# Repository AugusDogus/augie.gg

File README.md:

# augie.gg

My personal website.

## Tech Stack

- [Next.js 16](https://nextjs.org)
- [Tailwind CSS](https://tailwindcss.com)
- [Radix UI](https://www.radix-ui.com) primitives
- [MDX](https://mdxjs.com)
- [sugar-high](https://github.com/huozhi/sugar-high)
- [Phosphor Icons](https://phosphoricons.com)
- Inter and Geist Mono, self-hosted with their OFL licenses

## Projects

The home page is generated from [`src/content/projects.ts`](src/content/projects.ts),
the only file to edit.

To add a project, insert an entry in date order (newest first):

```ts
{
  title: "my-project",
  href: "https://github.com/AugusDogus/my-project", // omit for private repos
  date: "2026-10-11", // first authored commit
  blurb: "One sentence. Inline [links](https://example.com) work.",
  labels: ["wip"], // wip | active | archived | oss | pending
  private: true, // shows a private repository note
  fork: true, // name upstream in the blurb
},
```

Everything lands in the expandable Everything else section, grouped by year, unless you mark it:

- `featured: n` moves it into **Selected work** at position `n` (1 is first).
  Add a `highlight`: one line of concrete, verifiable evidence such as the
  stack, a hard problem, or real usage. Don't invent numbers.
- `notable: n` names a merged upstream contribution at position `n` of the OSS
  line under Selected work. Set `contributionName` for its short display label
  and link `href` directly to the merged PR. It also stays in Everything else.

## Development

```bash
bun install
bun dev
```

No environment variables are required. To show the GitHub activity graph, set
`GITHUB_TOKEN` to a classic personal access token with no scopes (see
`.env.example`); without it the panel is hidden and the rest of the page is
unchanged.

```bash
bun run check
bun test
bun run format:check
bun run build
```

## Design and artwork

The interface is dark glass (`.material` in `src/styles/globals.css`) over a
scrim that leaves the painting clear on the right. Inter's display cut sets the
name; Geist Mono only draws keyboard hints.

- ⌘K (or Ctrl K, or /) opens a command menu over actions, selected work, open
  source contributions, and every other project.
- Every project opens in one project view (`ProjectView` in
  `src/components/work/project-view.tsx`): its captures on top, then status,
  title, start date, blurb, evidence, and a link out. Rows, the command menu,
  the archive, and `?p=<title>` links all open it.
- On wide screens with a mouse the view lives on a stage beside the list,
  over the painting. Hovering or focusing a row previews the project there;
  clicking it or pressing Enter pins it, which selects the row, adds previous,
  next, and close buttons, writes `?p=`, and lets ← → step and Esc close.
  While a project is pinned, hovering other rows leaves the stage alone. The
  pointer can cross from a row onto the stage, even diagonally over other
  rows, without losing the preview.
- On phones, tablets, and narrow windows rows carry a thumbnail instead, and
  the same view opens in a draggable bottom sheet.
- Captures share one frame whether they are images or videos, with a phone
  capture set in front of the lead screen as picture-in-picture. Videos play
  only while on screen, and show their poster with reduced motion or
  Save-Data. A hairline under a playing composition fills as its loop runs
  and holds while the animation is paused.
- While a capture is still loading, the painting's mother and calf swim in
  its frame (`WhaleLoader`), and the capture fades in over them. The same
  whale model prints them once, in a worker, as a dithered strip that CSS
  steps through, so they keep time while the page is busy. They wait 400ms
  before appearing, so a capture that is only a little late never shows them.
- Where projects open in the sheet, the featured projects' captures are
  fetched once the page has loaded and settled, and an open project's
  neighbours' as it opens (`Warm`), so the sheet usually opens onto them.
  Nothing is fetched ahead with Save-Data.
- A link to an open project, `/?p=<title>`, previews with that project's own
  card (`ProjectCard`), drawn as the site shows the project: its name and
  blurb at the left over the site's background, and its lead capture at the
  right in the site's glass panel, with its status and when it began. The
  name is set as large as fits and breaks only between words. `next.config.js` rewrites the link to `/p/[...title]`, which is
  home under that project's metadata, and `/og/[...title]` draws every card
  at build.
- Where a preview plays video, a project whose lead capture is a clip
  previews with its card and the clip playing in it:
  `public/og-video/<project>.mp4`. `bun run og:projects` renders them all
  (it needs ffmpeg), and `bun test` fails when a card, a clip or a blurb has
  changed since.
- A link to the site itself previews with the home card, and where a preview
  plays video the card's painting moves: `og:video` points at
  `public/og-video.mp4`. It runs for one pass of the mother and calf, about
  31 seconds, and its end meets its start in the moment between passes when
  neither shows (`Pass`), so it loops with no whale in two places.
  `bun run og:video` draws it on the site's own renderer, sets it in the
  site's own background (taken from the built site, so run `bun run build`
  first), and writes its first frame as the card,
  `src/app/opengraph-image.jpg`, so the two cannot differ. The same frame
  without the words, `src/assets/card-backdrop.jpg`, is what every project's
  card is drawn on. It needs `CHROME_PATH` set to a Chrome or Chromium
  binary, and ffmpeg. Run it again after a change to how the painting or the
  site's background looks, or how the pod swims.
- The open project's controls include a share button: a phone gets the
  system's share sheet, everything else copies the `?p=` link and says so.
- Copying the email makes the whales in view flick their flukes.
- On the 404 page the loader's mother and calf swim over the card's glass,
  above the message. The painting plays there too, with the dock to pause it.
- The console greets whoever opens it with the whales as text and a link to
  this repository.
- The activity panel prints the last year of GitHub contributions with streaks
  and the busiest day, readable by hover, touch, or arrow keys.
- The dock pauses the painting (or press P), credits it, and shows the time in
  Pensacola.
- The name is one element to a navigation between home and the résumé, so
  it travels to its new place and size (`NameHeading`, a view transition)
  while the rest of the page changes under it.
- On wide screens the search and GitHub buttons stay pinned as the page
  scrolls, like the dock.

The résumé remains in `src/app/resume/page.mdx` on the same glass. Print styles
keep it in a single black-on-white column on one US Letter page.

The résumé's PDF button opens `public/resume.pdf` in a new tab, to print or
save from the browser's viewer. It is that print committed as a file, with
links within the site pointed at augie.gg. A deploy
has no browser to print with, so print it again after changing the résumé:

```sh
bun run build && CHROME_PATH=<chrome or chromium binary> bun run resume:pdf
```

A test fails while the file is older than `page.mdx` or `resume.css`.

The résumé's Twitch line shows the channel's subscriber badge with the months
on hover, the months beside it on touch screens, and the words alone in print.

The background uses Kazu Kibuishi's _Flight_ artwork, linked to its
[Gallery Nucleus listing](https://www.gallerynucleus.com/detail/2126/).
The artwork belongs to its artist, not this repository's code license.
Fonts and their licenses live in `src/assets/fonts`.

`src/styles/flight-poster.css` embeds the initial filtered frame (AVIF) and a
small backdrop (WebP) in the render-blocking stylesheet. This makes the first
paint complete without waiting for image requests or animation JavaScript.
The live canvas replaces it only after its first draw; its sizing, shading,
and masks match the poster.

`src/lib/flight` prints everything onto the painting's two-pixel dither:

- Three air currents: twisted ribbons of bead fibers, after React Bits'
  [Ghost Fibers](https://reactbits.dev/backgrounds/ghost-fibers), drawn as GPU
  points into one texel per dither cell. Fibers bunch into bright folds where a
  ribbon turns edge-on. Their ink lightens dark paint and sinks into bright
  sky, and layered masks let them pass behind clouds and the bird's wing.
- A whale pod (a mother and calf, a pale drift whale, and a distant traveller)
  rigged on spines that follow the currents. Tail strokes send a wave down each
  body; whales glide once the current carries them, part its fibers, and leave
  folds in their wake. The drift whale is cued so a whale is always swimming.
- The painting's own whales and bird flocks move: their pixels are re-printed
  from the continuous paint at a displaced position onto the same fixed dither
  cells, so flukes beat without the dots swimming.
- The cursor is an instrument. Sweeping across a current plucks it, resting on
  one parts it, whales turn toward a slow cursor and startle at a fast one,
  painted whales stroke harder nearby, and dragging in open sky draws a ribbon
  that drifts off as a gust. Taps work on touch without blocking scrolling.
- Wind displacement, cursor combing, and drifting specks.

The animation runs at up to 60 fps and stops when the tab is
hidden, when paused, or when reduced motion is requested. Without WebGL, or
while a lost GPU context recovers, a 2D path draws the print, flat whale
silhouettes, and specks. Loading or canvas failure preserves the pre-rendered
background. React cleanup releases listeners, observers, frame callbacks, and
GPU resources. Tests cover routes and their clearance around the UI, whale
kinematics, moods and rigging, painted-subject mattes, input gestures, pod
timing and coverage, frame pacing, and poster freshness. In development,
`flight.captureScript(events, shots)` replays scripted pointer events on the
fixed clock and returns frames, for judging interactions frame by frame.

### Poster

The painting shows three things in turn: a 1 KB blurred placeholder inline in
the stylesheet, the poster (`src/assets/flight-poster.avif`, faded in when it
loads), and then the live canvas, drawn by a worker (`src/lib/flight/worker.ts`)
so the page's main thread never waits on WebGL.

`bun test` fails when the model, shader, or speck inputs of the t=0 frame
change, because the poster would no longer match the first live frame.
Changes to the print bake in `texture.ts` or to the speck painter need the same
recapture, by hand:

1. Run `bun dev`, open `/`, and run `await flight.capturePoster()` in the
   browser console. It downloads `flight-poster.png`, the 1200×874 frame before
   viewport scaling and feathering.
2. Run `bun scripts/flight-poster.ts ~/Downloads/flight-poster.png`. It needs
   `avifenc` (libavif) and `magick` (ImageMagick), and rewrites the AVIF, the
   placeholder, and `poster-key` in `flight-poster.css`.

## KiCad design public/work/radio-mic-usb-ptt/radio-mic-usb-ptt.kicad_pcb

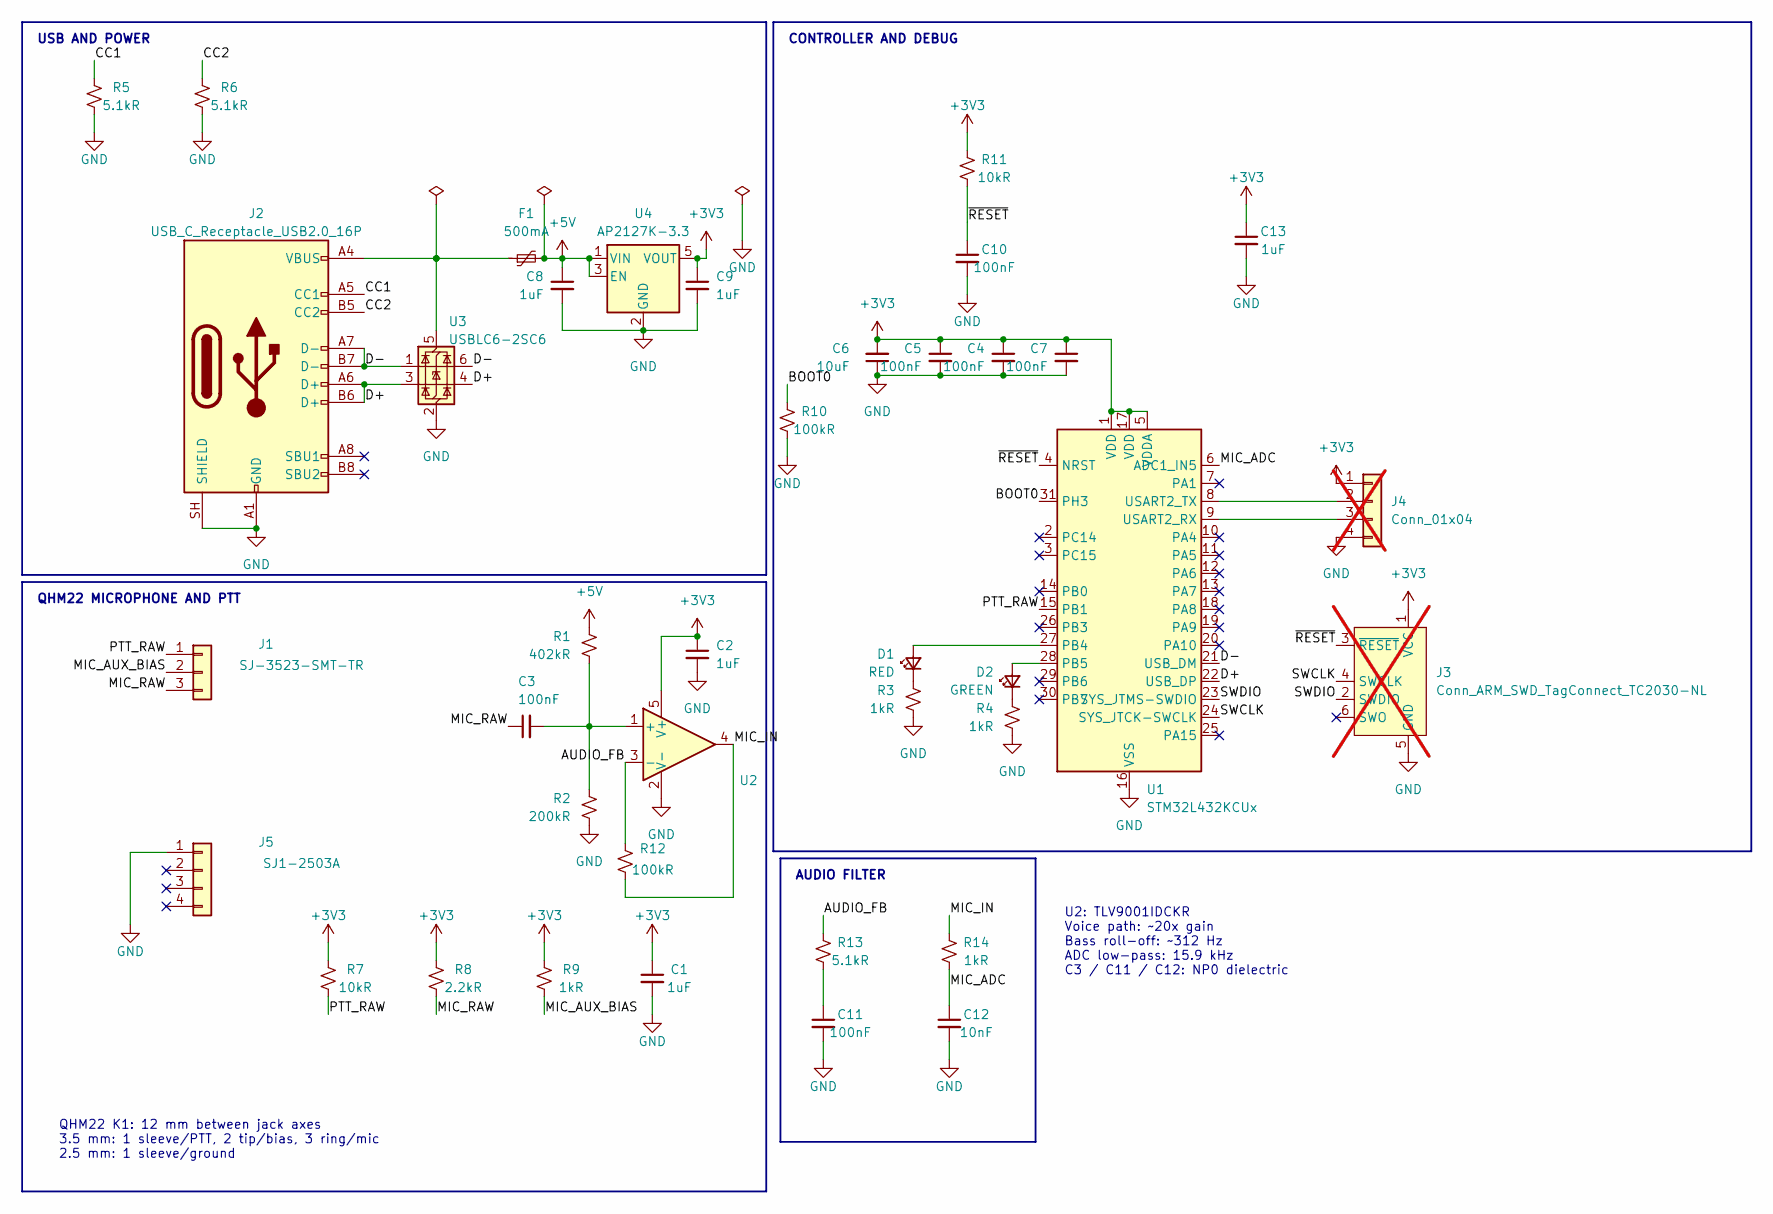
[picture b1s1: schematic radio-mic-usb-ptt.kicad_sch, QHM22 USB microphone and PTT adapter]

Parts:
C1, C2, C8, C9, C13: 1uF; C_0603_1608Metric; MPN CL10B105KB8NQNC; LCSC C5199872
C3, C11: 100nF; C_1206_3216Metric; MPN 1206N104J500CT; LCSC C170182
C4, C5, C7, C10: 100nF; C_0603_1608Metric; MPN CC0603KRX7R9BB104; LCSC C14663
C6: 10uF; C_0603_1608Metric; MPN CL10A106MA8NRNC; LCSC C96446
C12: 10nF; C_0603_1608Metric; MPN 0603N103J500CT; LCSC C2894187
D1: RED; D_0603_1608Metric; MPN KT-0603R; LCSC C2286
D2: GREEN; D_0603_1608Metric; MPN KT-0603G; LCSC C12624
F1: 500mA; Fuse_0805_2012Metric; MPN SMD0805B050TF; LCSC C269104
J1: SJ-3523-SMT-TR; Jack_3.5mm_SameSky_SJ-3523-SMT-TR; MPN SJ-3523-SMT-TR
J2: USB_C_Receptacle_USB2.0_16P; USB_C_HRO_TYPE-C-31-M-12_EdgeSilk; MPN TYPE-C-31-M-12; LCSC C165948
J3: Conn_ARM_SWD_TagConnect_TC2030-NL; Tag-Connect_TC2030-IDC-NL_2x03_P1.27mm_Vertical; not fitted
J4: Conn_01x04; PinHeader_1x04_P2.54mm_Vertical; not fitted
J5: SJ1-2503A; Jack_2.5mm_SameSky_SJ1-2503A; MPN SJ1-2503A
R1: 402kR; R_0603_1608Metric; MPN RT0603BRD07402KL; LCSC C705774
R2: 200kR; R_0603_1608Metric; MPN RT0603BRD07200KL; LCSC C728585
R3, R4, R9, R14: 1kR; R_0603_1608Metric; MPN RT0603BRD071KL; LCSC C110776
R5, R6, R13: 5.1kR; R_0603_1608Metric; MPN RT0603BRD075K1L; LCSC C122969
R7, R11: 10kR; R_0603_1608Metric; MPN RT0603BRD0710KL; LCSC C95204
R8: 2.2kR; R_0603_1608Metric; MPN RT0603BRD072K2L; LCSC C861295
R10, R12: 100kR; R_0603_1608Metric; MPN RT0603BRD07100KL; LCSC C122538
U1: STM32L432KCUx; QFN-32-1EP_5x5mm_P0.5mm_EP3.45x3.45mm; MPN STM32L432KCU6; LCSC C1337280
U2: TLV9001IDCK; SOT-353_SC-70-5; MPN TLV9001IDCKR; LCSC C398362
U3: USBLC6-2SC6; SOT-23-6; MPN USBLC6-2SC6; LCSC C7519
U4: AP2127K-3.3; SOT-23-5; MPN AP2127K-3.3TRG1; LCSC C156285

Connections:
+3V3: C1.1, C2.1, C4.1, C5.1, C6.2, C7.1, C9.1, C13.1, J3.1 (VCC), J4.1, R7.1, R8.1, R9.1, R11.1, U1.1 (VDD), U1.5 (VDDA), U1.17 (VDD), U2.5 (V+), U4.5 (VOUT)
+5V: C8.1, F1.2, R1.1, U4.1 (VIN), U4.3 (EN)
/AUDIO_FB: R12.1, R13.1, U2.3 (-)
/BOOT0: R10.1, U1.31 (PH3)
/CC1: J2.A5 (CC1), R5.1
/CC2: J2.B5 (CC2), R6.1
/D+: J2.A6 (D+), J2.B6 (D+), U1.22 (PA12), U3.3 (I/O2), U3.4 (I/O2)
/D-: J2.A7 (D-), J2.B7 (D-), U1.21 (PA11), U3.1 (I/O1), U3.6 (I/O1)
/MIC_ADC: C12.1, R14.2, U1.6 (PA0)
/MIC_AUX_BIAS: J1.2, R9.2
/MIC_IN: R12.2, R14.1, U2.4
/MIC_RAW: C3.1, J1.3, R8.2
/PTT_RAW: J1.1, R7.2, U1.15 (PB1)
/SWCLK: J3.4 (SWCLK), U1.24 (PA14)
/SWDIO: J3.2 (SWDIO), U1.23 (PA13)
/~RESET: C10.1, J3.3 (~RESET), R11.2, U1.4 (NRST)
GND: C1.2, C2.2, C4.2, C5.2, C6.1, C7.2, C8.2, C9.2, C10.2, C11.2, C12.2, C13.2, J2.A1 (GND), J2.A12 (GND), J2.B1 (GND), J2.B12 (GND), J2.SH (SHIELD), J3.5 (GND), J4.4, J5.1, R2.2, R3.2, R4.2, R5.2, R6.2, R10.2, U1.16 (VSS), U1.32 (VSS), U1.33 (VSS), U2.2 (V-), U3.2 (GND), U4.2 (GND)
unnamed: C11.1, R13.2
unnamed: D1.2 (A), U1.27 (PB4)
unnamed: D1.1 (K), R3.1
unnamed: D2.2 (A), U1.28 (PB5)
unnamed: D2.1 (K), R4.1
unnamed: J4.2, U1.8 (PA2)
unnamed: J4.3, U1.9 (PA3)
unnamed: C3.2, R1.2, R2.1, U2.1 (+)
unnamed: F1.1, J2.A4 (VBUS), J2.A9 (VBUS), J2.B4 (VBUS), J2.B9 (VBUS), U3.5 (VBUS)

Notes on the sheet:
QHM22 K1: 12 mm between jack axes 3.5 mm: 1 sleeve/PTT, 2 tip/bias, 3 ring/mic 2.5 mm: 1 sleeve/ground
U2: TLV9001IDCKR Voice path: ~20x gain Bass roll-off: ~312 Hz ADC low-pass: 15.9 kHz C3 / C11 / C12: NP0 dielectric
USB AND POWER
CONTROLLER AND DEBUG
QHM22 MICROPHONE AND PTT
AUDIO FILTER

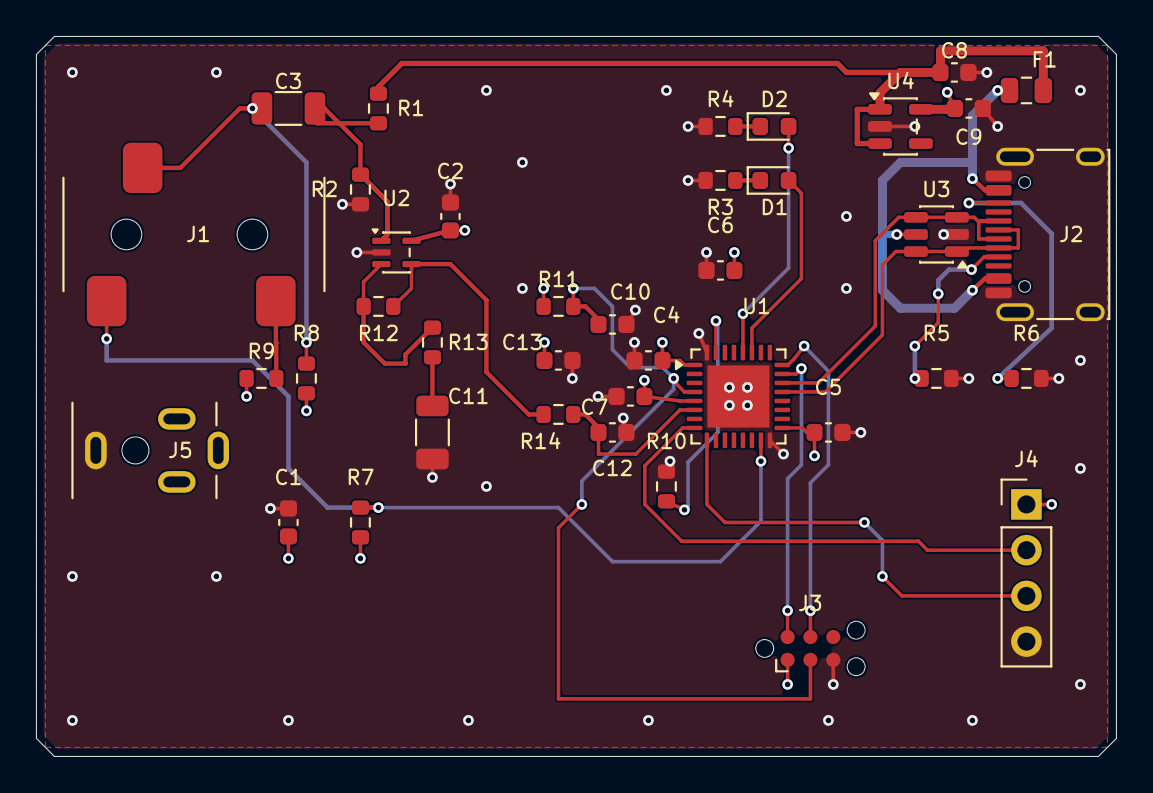
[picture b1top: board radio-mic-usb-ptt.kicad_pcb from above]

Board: 4 copper layers, 60.0 x 40.0 mm, 39 parts (0 on the bottom side), 26 nets.

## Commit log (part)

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2026-01-10 init: project
2026-01-10 feat(ui): add shadcn/ui
2026-01-10 feat(blog): convert t3 boilerplate to personal blog/portfolio
    - Remove tRPC and related dependencies in favor of MDX-based content
    - Add MDX support with sugar-high syntax highlighting
    - Create age counter component with live updating display
    - Add theme toggle for dark/light mode with localStorage persistence
    - Create footer with social links (GitHub, Twitter, LinkedIn, Email, Discord)
    - Add dynamic blog post discovery from filesystem
2026-01-10 fix(ui): resolve hydration errors and improve UX
    - Fix Discord URL protocol (http → https) to prevent hydration mismatch
    - Add custom Table component for MDX to avoid whitespace hydration errors
    - Fix blog card hover flickering by applying styles directly to Link
    - Add animated transition to theme toggle icon
    - Refactor Header component to use usePathname for home link visibility
    - Add blog post: Reverse Engineering Neewer Lights
2026-01-10 refactor(theme): use next-themes and fix age counter hydration
    - Replace custom theme logic with next-themes for proper SSR support
    - Add ThemeProvider wrapper in root layout
    - Simplify ThemeToggle to use useTheme hook with CSS-based icon transitions
    - Fix age counter hydration using inline script trick (no flash, no mismatch)
    - Add space-y-4 to blog layout for paragraph spacing
    - Adjust h1 padding in MDX components
2026-01-10 feat(avatar): add interactive avatar with morph effect and dynamic favicon
    - Add Avatar component with hover-triggered morph/dissolve transition
    - Swap favicon dynamically between IRL photo and avatar on hover
    - Replace default favicon.ico with pfp.png
    - Adjust layout padding and footer margin for better spacing
2026-01-10 feat(resume): add dedicated resume page with MDX rendering
    - Create /resume page with full resume content in MDX format
    - Add resume layout with header navigation
    - Add inline "Full resume →" link in Work section header on homepage
2026-01-10 refactor(avatar): use pre-cropped circular images instead of runtime canvas
    - Replace square images with full-res circular versions via ImageMagick
    - Remove canvas-based circular cropping code (~40 lines)
    - Simplify favicon swap to direct href assignment
2026-01-10 chore(seo): update site description
    - Change meta description to "🍄 Learning • Building • Writing"
2026-01-10 docs(readme): replace T3 boilerplate with project-specific readme
2026-01-10 fix(blog): use RegExp.exec() instead of String.match()
    - Fix @typescript-eslint/prefer-regexp-exec lint errors
2026-01-10 feat(home): replace Stack section with Projects
    - Add opentab.sh, whisp.chat, and santahat.gg project links
    - Add GitHub profile link in section header
    - Remove tech stack listing
2026-01-10 style(mobile): improve responsive design for mobile devices
    - Reduce text sizes on mobile (headings, body, lists)
    - Shrink avatar from 96px to 64px on mobile
    - Add top padding on mobile to prevent toggle overlap
    - Position theme toggle absolutely on mobile homepage
    - Reduce vertical spacing between sections on mobile
    - Remove footer margin on mobile
2026-01-10 style(footer): add mobile margin
    - Add mt-2 margin on mobile for footer spacing
2026-01-10 feat(blog): add reading time and progress bar to posts
    - Add calculateReadingTime utility using 225 wpm default
    - Create ReadingProgress component with scroll-based tracking
    - Use requestAnimationFrame for smooth progress updates
    - Respect prefers-reduced-motion for accessibility
    - Handle short posts, dynamic content, and route transitions
    - Display reading time near post title
2026-01-10 feat: Add project dependencies to package-lock.json
2026-01-10 fix(blog): move reading time util to client-safe module
    Separates calculateReadingTime into its own file without fs import
    to allow use in client components without Node.js module errors.
2026-01-10 chore: remove package-lock.json, project uses bun
    Add package-lock.json to .gitignore to prevent conflicts with bun.lock.
2026-01-10 fix(a11y): make prefers-reduced-motion reactive
    Use MediaQueryList change listener to respond dynamically when user
    toggles their motion preference, instead of checking only on mount.
2026-01-10 fix(blog): include code blocks in reading time calculation
    Only strip metadata export and imports from word count, keeping
    code blocks and JSX content to match original DOM-based calculation.
2026-01-10 refactor(blog): simplify reading time to MDX component
    Use a simple ReadingTime MDX component with hardcoded minutes value
    instead of runtime calculation. Works with mdxRs, no extra deps needed.
2026-01-10 chore: update dependencies in bun.lock
    Update bun.lock and minor refactors during reading time implementation.
2026-01-10 refactor(blog): calculate reading time at build time
    - Move MDX files to src/content/blog/
    - Add dynamic [slug] route that reads MDX source at build time
    - Calculate reading time from raw MDX content during static generation
    - Update blog.ts to read from new content folder location
2026-01-10 fix(security): prevent path traversal via dynamicParams=false
    Set dynamicParams=false to restrict blog routes to pre-generated
    slugs only, preventing potential path traversal attacks via the
    slug parameter.
2026-01-31 feat(footer): add Spotify profile link
    - Add SpotifyLogo icon import from phosphor-icons
    - Add Spotify social link to footer with aurothic profile URL
2026-02-13 docs(blog): add MCP server in 30 minutes blog post
2026-02-13 feat(blog): show only latest post on homepage and add blog index page
    - Refactor homepage Writing section to display single latest post with "Blog →" link
    - Create /blog index page that lists all posts
    - Match Writing section header style to Work and Projects sections
2026-02-13 fix(blog): remove metadata export from blog index page
2026-02-13 refactor(blog): move reading progress bar from shared layout to individual post pages
    - Remove BlogArticle wrapper from blog layout so it no longer applies to /blog index
    - Wrap individual post content in BlogArticle in [slug]/page.tsx
2026-02-13 feat(header): replace back link with path-based breadcrumb navigation
    - Generate breadcrumbs from URL segments (e.g. Home / Blog / Post Title)
    - Make intermediate segments clickable links, current page displayed as plain text
    - Truncate long segment names to 200px to keep header tidy
2026-02-13 style(homepage): clamp blog post card title and description to 2 lines
    - Add line-clamp-2 to CardTitle and CardDescription on homepage blog card
2026-02-13 chore(homepage): replace santahat.gg with junkyardindex.com in projects list
    - Update project link, name, and description to Junkyard Index
2026-04-07 Fix Neewer light app blog link
2026-04-07 Extract animated hero into reusable client component
    - Move the home page intro into `Hero`
    - Add hover-driven avatar title and favicon swap
    - Animate the displayed name between full name and handle
2026-04-07 Extract scramble text animation into reusable component
    - Move hero name scrambling logic into `ScrambleText`
    - Keep layout width reserved while animating between name and handle
2026-04-07 Centralize app title constants
    - Reuse shared title values in layout and avatar hover state
    - Keep the scramble text fallback from ever returning `undefined`
2026-04-07 Refresh theme tokens and add subtle page texture
    - Rework light and dark CSS variables around the new palette
    - Add a faint fixed noise overlay for more visual depth
    - Remove the obsolete MCP server blog post
2026-04-16 content(blog): rewrite Neewer lights post in a more natural voice
    Tightens paragraphs, adds colon-driven setup/payoff beats, restructures
    sections to lead with the outcome, removes em dashes, and corrects the
    attribution so Frida is credited to me rather than Claude.
2026-06-03 revert(theme): restore neutral primary and ring tokens
    - Revert --primary to near-black (light) / near-white (dark)
    - Revert --ring to mid-neutral grays in both modes
    - Revert --sidebar-primary and --sidebar-ring to match
    - Remove blue accent from reading progress bar, buttons, link hovers, and focus rings
